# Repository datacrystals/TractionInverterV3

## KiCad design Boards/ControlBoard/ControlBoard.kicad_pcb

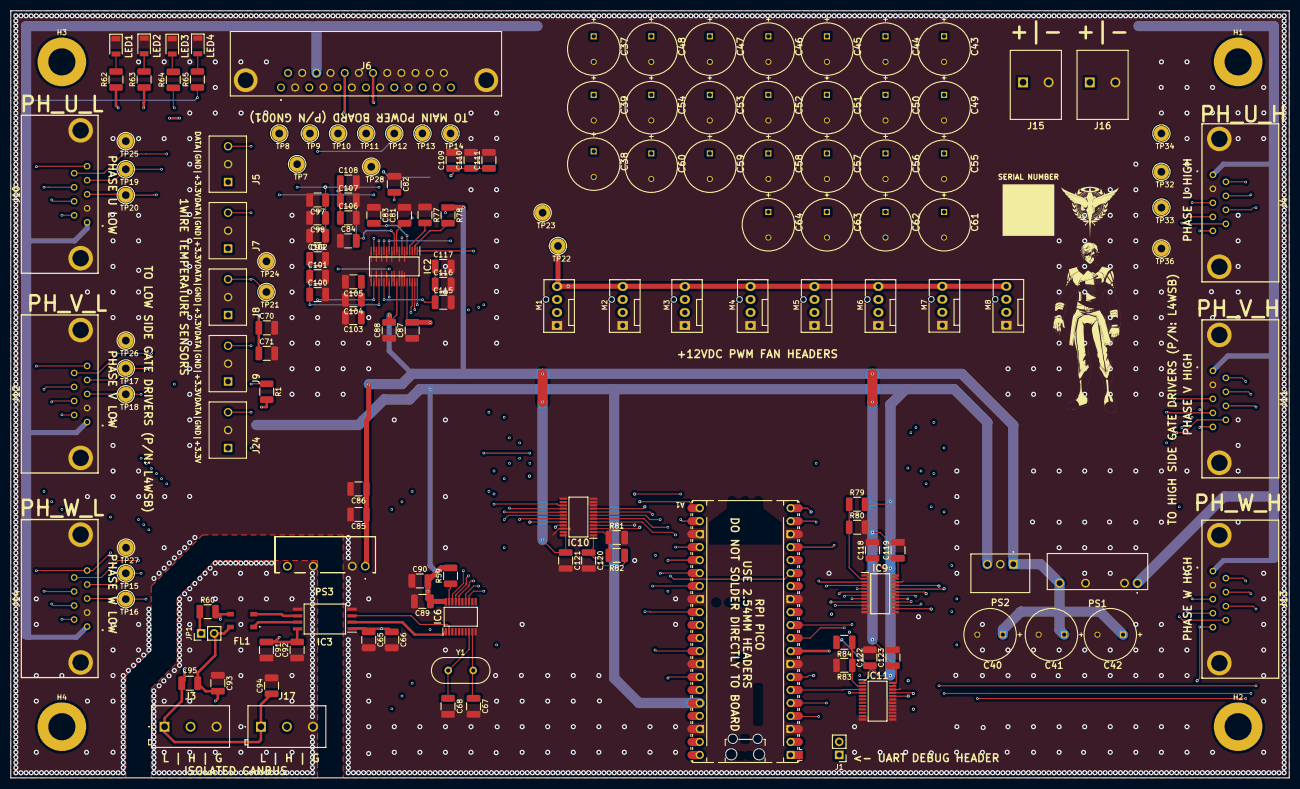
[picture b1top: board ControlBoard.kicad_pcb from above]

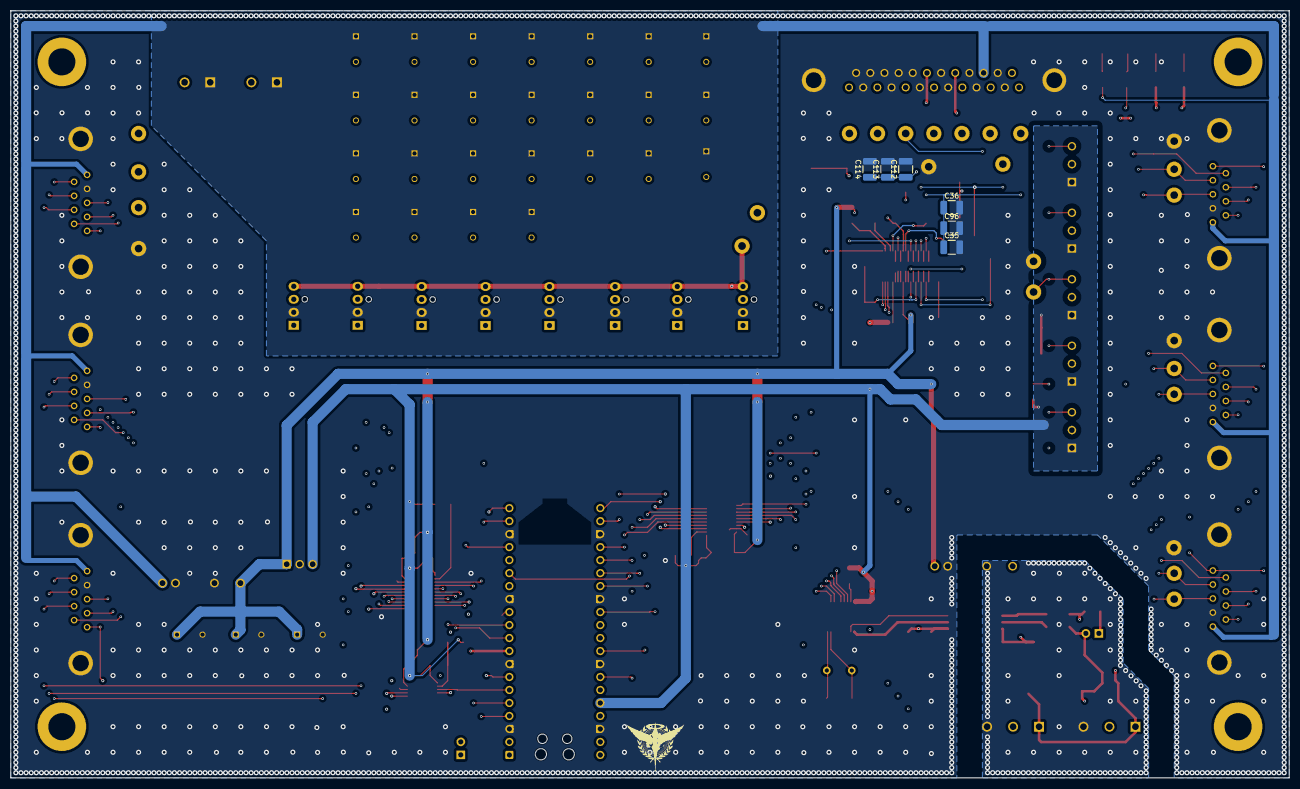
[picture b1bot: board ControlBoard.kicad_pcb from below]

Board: 4 copper layers, 250.0 x 150.0 mm, 166 parts (6 on the bottom side), 81 nets.

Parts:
A1: RaspberryPi_Pico; RaspberryPi_Pico_Common_Unspecified
C35, C97, C100, C103, C106, C109, C112, C115: 1nF; C_1210_3225Metric_Pad1.33x2.70mm_HandSolder
C36, C98, C101, C104, C107, C110, C113, C116: 10nF; C_1210_3225Metric_Pad1.33x2.70mm_HandSolder
C37, C38, C39, C40, C41, C42, C43, C44, C45, C46, C47, C48, C49, C50, C51, C52, C53, C54, C55, C56, C57, C58, C59, C60, C61, C62, C63, C64: UVY1E102MPD1TD; CAPPRD500W60D1025H1750
C65, C70, C81, C82, C83, C84, C85, C87, C88, C89, C92, C96, C99, C102, C105, C108, C111, C114, C117, C118, C119, C120, C121, C122, C123: 100nF; C_1210_3225Metric_Pad1.33x2.70mm_HandSolder
C66, C71, C86, C90, C91: 10uF; C_1210_3225Metric_Pad1.33x2.70mm_HandSolder
C67, C68, C93, C94, C95: 22pF; C_1210_3225Metric_Pad1.33x2.70mm_HandSolder
FL1: ACT45B-101-2P-TL003; ACT45B1012PTL003
H1, H2, H3, H4: MountingHole_Pad; MountingHole_5.3mm_M5_ISO7380_Pad
IC2: ADS8688AIDBT; SOP50P640X120-38M
IC3: ISO1042BDWVR; SOIC127P1150X280-8N
IC6: MCP2515-e_ST; SOP65P640X120-20N
IC9, IC10, IC11: SN74LXCH8T245PWR; SOP65P640X120-24N
J1: Conn_01x02_Pin; PinHeader_1x02_P2.54mm_Vertical
J3, J17: 1548129
J4, J10, J11, J12, J13, J14: 5-106505-2; 5-106505-2_3
J5, J7, J8, J9, J24: 5442251
J6: L717SDB25PA4CH3R
J15, J16: 1987724
JP1: Jumper_2_Open; PinHeader_1x02_P2.54mm_Vertical
LED1: LTST-C230CKT; LEDC3216X120N
LED2, LED3, LED4: LTST-C230GKT; LEDC3216X120N
M1, M2, M3, M4, M5, M6, M7, M8: Fan_4pin; FanPinHeader_1x04_P2.54mm_Vertical
PS1: RKE-1205S_H; RKE1205SH
PS2: R-78K3.3-1.0; R78K3310
PS3: RFMM-0505S; RFMM0505S
R1, R59, R77, R78, R79, R80, R81, R82, R83, R84: 4.7k; R_1210_3225Metric_Pad1.30x2.65mm_HandSolder
R60: 120; R_1210_3225Metric_Pad1.30x2.65mm_HandSolder
R62, R63, R64: 220; R_1210_3225Metric_Pad1.30x2.65mm_HandSolder
R65: 1k; R_1210_3225Metric_Pad1.30x2.65mm_HandSolder
TP7, TP8, TP9, TP10, TP11, TP12, TP13, TP14, TP15, TP16, TP17, TP18, TP19, TP20, TP21, TP22, TP23, TP24, TP25, TP26, TP27, TP28, TP32, TP33, TP34, TP36: TestPoint; TestPoint_Loop_D2.54mm_Drill1.5mm_Beaded
Y1: 8MHz; Crystal_HC49-4H_Vertical

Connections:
1WIRE_3v3_DATA: A1.20 (GPIO15), J5.3, J7.3, J8.3, J9.3, J24.3, R1.1, TP21.1
+3.3V: A1.36 (3V3), C65.1, C66.1, C70.1, C71.1, C87.2, C89.1, C90.2, C118.1, C120.1, C122.1, IC2.34 (DVDD), IC3.1 (VCC1), IC6.20 (VDD), IC9.1 (VCCA), IC10.1 (VCCA), IC11.1 (VCCA), J5.1, J7.1, J8.1, J9.1, J24.1, PS2.3 (+VOUT), R1.2, R59.2, R79.2, R82.2, R84.2
+5V: C40.1 (+), C41.1 (+), C42.1 (+), C81.1, C85.1, C86.1, C88.2, C119.1, C121.1, C123.1, IC2.9 (AVDD_1), IC2.30 (AVDD_2), IC9.23 (VCCB_1), IC9.24 (VCCB_2), IC10.23 (VCCB_1), IC10.24 (VCCB_2), IC11.23 (VCCB_1), IC11.24 (VCCB_2), PS1.7 (+VOUT), PS2.1 (+VIN), PS3.1 (+VIN), R64.1, R78.1
+12V: C37.1 (+), C38.1 (+), C39.1 (+), C43.1 (+), C44.1 (+), C45.1 (+), C46.1 (+), C47.1 (+), C48.1 (+), C49.1 (+), C50.1 (+), C51.1 (+), C52.1 (+), C53.1 (+), C54.1 (+), C55.1 (+), C56.1 (+), C57.1 (+), C58.1 (+), C59.1 (+), C60.1 (+), C61.1 (+), C62.1 (+), C63.1 (+), C64.1 (+), J4.1, J6.23, J10.1, J11.1, J12.1, J13.1, J14.1, J15.1, J16.1, M1.2 (+), M2.2 (+), M3.2 (+), M4.2 (+), M5.2 (+), M6.2 (+), M7.2 (+), M8.2 (+), PS1.1 (+VIN), R65.1
ADC_SPI_CS: A1.19 (GPIO14), IC2.38 (~CS)
CANBUS_ISO_5V: C91.1, C92.2, IC3.8 (VCC2), PS3.7 (+VOUT)
CANBUS_ISO_GND: C91.2, C92.1, C93.1, C94.2, IC3.5 (GND2), J3.3, J17.3, PS3.5 (-VOUT)
CAN_CS: A1.32 (GPIO27_ADC1), IC6.18 (~CS)
CAN_INT: A1.34 (GPIO28_ADC2), IC6.13 (~INT)
CanH_External: C93.2, C95.1, FL1.4, J3.2, J17.2, JP1.2 (B)
CanL_External: C94.1, C95.2, FL1.3, J3.1, J17.1, R60.2
DC_LINK_BUS_CURRENT_SENSE: C35.1, C36.1, C96.1, IC2.18 (AIN_1P), J6.1, TP8.1
DC_LINK_BUS_ISOLATED_VSENSE: C97.1, C98.1, C99.1, IC2.16 (AIN_0P), J6.25, TP7.1
FAN_3v3_PWM: A1.21 (GPIO16), IC10.3 (A1)
FAN_PWM: IC10.21 (B1), M1.4 (PWM), M2.4 (PWM), M3.4 (PWM), M4.4 (PWM), M5.4 (PWM), M6.4 (PWM), M7.4 (PWM), M8.4 (PWM), TP22.1
FAULT_3v3_INPUT: A1.31 (GPIO26_ADC0), IC11.4 (A2)
FAULT_INPUT: IC11.20 (B2), J4.5, J10.5, J11.5, J12.5, J13.5, J14.5
FAULT_LED: J6.21, R62.1
GATE_SPI_3v3_RX: A1.6 (GPIO4), IC11.3 (A1)
GATE_SPI_3v3_SCK: A1.4 (GPIO2), IC9.3 (A1)
GATE_SPI_3v3_TX: A1.5 (GPIO3), IC9.4 (A2)
GATE_SPI_RX: IC11.21 (B1), J4.6, J10.6, J11.6, J12.6, J13.6, J14.6, TP34.1
GATE_SPI_SCK: IC9.21 (B1), J4.8, J10.8, J11.8, J12.8, J13.8, J14.8, TP33.1
GATE_SPI_TX: IC9.20 (B2), J4.7, J10.7, J11.7, J12.7, J13.7, J14.7, TP32.1
GATE_U_3v3_H_CS: A1.9 (GPIO6), IC9.6 (A4)
GATE_U_3v3_L_CS: A1.7 (GPIO5), IC9.5 (A3)
GATE_U_H_CS: IC9.18 (B4), J4.9
GATE_U_L_CS: IC9.19 (B3), J10.9
GATE_V_3v3_H_CS: A1.11 (GPIO8), IC9.8 (A6)
GATE_V_3v3_L_CS: A1.10 (GPIO7), IC9.7 (A5)
GATE_V_H_CS: IC9.16 (B6), J11.9
GATE_V_L_CS: IC9.17 (B5), J12.9
GATE_W_3v3_H_CS: A1.17 (GPIO13), IC9.10 (A8)
GATE_W_3v3_L_CS: A1.12 (GPIO9), IC9.9 (A7)
GATE_W_H_CS: IC9.14 (B8), J13.9
GATE_W_L_CS: IC9.15 (B7), J14.9
GND: A1.3 (GND), A1.8 (GND), A1.13 (GND), A1.18 (GND), A1.23 (GND), A1.28 (GND), A1.33 (AGND), A1.38 (GND), C35.2, C36.2, C37.2 (-), C38.2 (-), C39.2 (-), C40.2 (-), C41.2 (-), C42.2 (-), C43.2 (-), C44.2 (-), C45.2 (-), C46.2 (-), C47.2 (-), C48.2 (-), C49.2 (-), C50.2 (-), C51.2 (-), C52.2 (-), C53.2 (-), C54.2 (-), C55.2 (-), C56.2 (-), C57.2 (-), C58.2 (-), C59.2 (-), C60.2 (-), C61.2 (-), C62.2 (-), C63.2 (-), C64.2 (-), C65.2, C66.2, C67.2, C68.2, C70.2, C71.2, C81.2, C82.1, C83.1, C84.1, C85.2, C86.2, C87.1, C88.1, C89.2, C90.1, C96.2, C97.2, C98.2, C99.2, C100.2, C101.2, C102.2, C103.2, C104.2, C105.2, C106.2, C107.2, C108.2, C109.2, C110.2, C111.2, C112.2, C113.2, C114.2, C115.2, C116.2, C117.2, C118.2, C119.2, C120.2, C121.2, C122.2, C123.2, IC2.6 (REFGND), IC2.8 (AGND_1), IC2.11 (AUX_GND), IC2.13 (AIN_6GND), IC2.15 (AIN_7GND), IC2.17 (AIN_0GND), IC2.19 (AIN_1GND), IC2.20 (AIN2_GND), IC2.22 (AIN_3GND), IC2.24 (AIN_4GND), IC2.26 (AIN_5GND), IC2.28 (AGND_2), IC2.29 (AGND_3), IC2.31 (AGND_4), IC2.32 (AGND_5), IC2.33 (DGND), IC3.4 (GND1), IC6.10 (VSS), IC9.11 (GND_1), IC9.12 (GND_2), IC9.13 (GND_3), IC9.22 (~OE), IC10.10 (A8), IC10.11 (GND_1), IC10.12 (GND_2), IC10.13 (GND_3), IC10.22 (~OE), IC11.11 (GND_1), IC11.12 (GND_2), IC11.13 (GND_3), IC11.14 (B8), IC11.15 (B7), IC11.16 (B6), IC11.17 (B5), IC11.18 (B4), IC11.19 (B3), IC11.22 (~OE), J4.2, J4.10, J4.11, J5.2, J6.2, J6.4, J6.6, J6.8, J6.10, J6.12, J6.14, J6.15, J6.16, J6.17, J6.18, J6.20, J6.22, J6.24, J6.MH1, J6.MH2, J7.2, J8.2, J9.2, J10.2, J10.10, J10.11, J11.2, J11.10, J11.11, J12.2, J12.10, J12.11, J13.2, J13.10, J13.11, J14.2, J14.10, J14.11, J15.2, J16.2, J24.2, LED1.1 (K), LED2.1 (K), LED3.1 (K), LED4.1 (K), M1.1 (-), M2.1 (-), M3.1 (-), M4.1 (-), M5.1 (-), M6.1 (-), M7.1 (-), M8.1 (-), PS1.2 (-VIN), PS1.5 (-VOUT), PS2.2 (GND), PS3.2 (-VIN), R77.1, R80.2, R81.2, R83.2, TP23.1, TP24.1, TP25.1, TP26.1, TP27.1, TP28.1, TP36.1
unnamed: A1.1 (GPIO0), J1.1
unnamed: A1.2 (GPIO1), J1.2
unnamed: C84.2, IC2.10 (AUX_IN)
unnamed: C82.2, IC2.7 (REFCAP)
unnamed: C83.2, IC2.5 (REFIO)
unnamed: IC2.4 (~REFSEL), R77.2
unnamed: IC2.2 (~RST/~PD), R78.2
unnamed: FL1.1, IC3.7 (CANH)
unnamed: FL1.2, IC3.6 (CANL)
unnamed: IC3.3 (RXD), IC6.2 (RXCAN)
unnamed: IC3.2 (TXD), IC6.1 (TXCAN)
unnamed: C67.1, IC6.9 (OSC1), Y1.2
unnamed: C68.1, IC6.8 (OSC2), Y1.1
unnamed: IC6.19 (~RESET), R59.1
unnamed: IC9.2 (DIR), R79.1, R80.1
unnamed: IC10.2 (DIR), R81.1, R82.1
unnamed: IC11.2 (DIR), R83.1, R84.1
unnamed: JP1.1 (A), R60.1
unnamed: LED1.2 (A), R62.2
unnamed: LED2.2 (A), R63.2
unnamed: LED3.2 (A), R64.2
unnamed: LED4.2 (A), R65.2
PHASE_U_ISENSE: C100.1, C101.1, C102.1, IC2.23 (AIN_3P), J6.3, TP9.1
PHASE_U_ISOLATED_VSENSE: C103.1, C104.1, C105.1, IC2.21 (AIN_2P), J6.9, TP12.1
PHASE_V_ISENSE: C106.1, C107.1, C108.1, IC2.27 (AIN_5P), J6.5, TP10.1
PHASE_V_ISOLATED_VSENSE: C115.1, C116.1, C117.1, IC2.25 (AIN_4P), J6.11, TP13.1
PHASE_W_ISENSE: C112.1, C113.1, C114.1, IC2.14 (AIN_7P), J6.7, TP11.1
PHASE_W_ISOLATED_VSENSE: C109.1, C110.1, C111.1, IC2.12 (AIN_6P), J6.13, TP14.1
PH_3v3_PWM_U_H: A1.26 (GPIO20), IC10.7 (A5)
PH_3v3_PWM_U_L: A1.22 (GPIO17), IC10.4 (A2)
PH_3v3_PWM_V_H: A1.27 (GPIO21), IC10.8 (A6)
PH_3v3_PWM_V_L: A1.24 (GPIO18), IC10.5 (A3)
PH_3v3_PWM_W_H: A1.29 (GPIO22), IC10.9 (A7)
PH_3v3_PWM_W_L: A1.25 (GPIO19), IC10.6 (A4)
PH_PWM_U_H: IC10.17 (B5), J4.3, J10.4, TP19.1
PH_PWM_U_L: IC10.20 (B2), J4.4, J10.3, TP20.1
PH_PWM_V_H: IC10.16 (B6), J11.3, J12.4, TP17.1
PH_PWM_V_L: IC10.19 (B3), J11.4, J12.3, TP18.1
PH_PWM_W_H: IC10.15 (B7), J13.3, J14.4, TP15.1
PH_PWM_W_L: IC10.18 (B4), J13.4, J14.3, TP16.1
SPI2_RX: A1.16 (GPIO12), IC2.36 (SDO), IC6.17 (SO)
SPI2_SCK: A1.14 (GPIO10), IC2.37 (SCLK), IC6.14 (SCK)
SPI2_TX: A1.15 (GPIO11), IC2.1 (SDI), IC6.16 (SI)
StatusLED: J6.19, R63.1

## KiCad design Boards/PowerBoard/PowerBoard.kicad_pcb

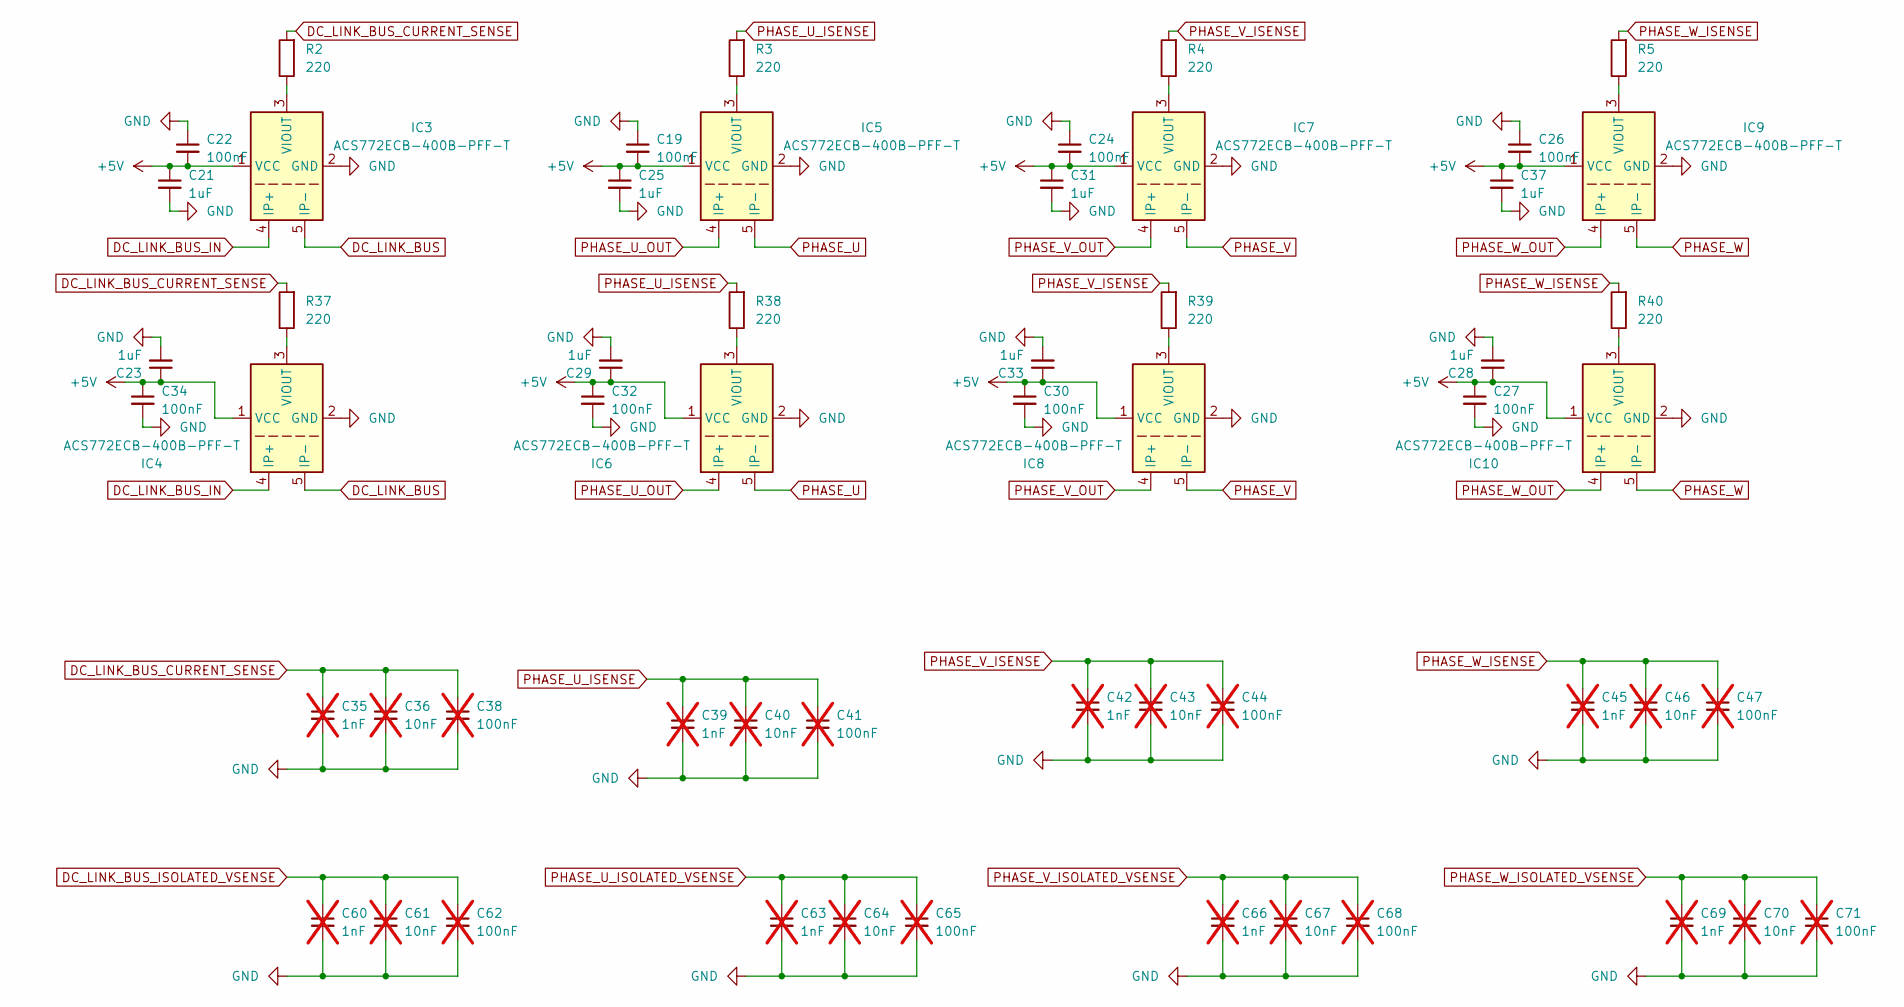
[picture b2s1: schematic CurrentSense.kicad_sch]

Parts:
C19, C22, C24, C26, C27, C30, C32, C34: 100nF; C_1210_3225Metric_Pad1.33x2.70mm_HandSolder
C21, C23, C25, C28, C29, C31, C33, C37: 1uF; C_1210_3225Metric_Pad1.33x2.70mm_HandSolder
C35, C39, C42, C45, C60, C63, C66, C69: 1nF; C_1210_3225Metric_Pad1.33x2.70mm_HandSolder; not fitted
C36, C40, C43, C46, C61, C64, C67, C70: 10nF; C_1210_3225Metric_Pad1.33x2.70mm_HandSolder; not fitted
C38, C41, C44, C47, C62, C65, C68, C71: 100nF; C_1210_3225Metric_Pad1.33x2.70mm_HandSolder; not fitted
IC3, IC4, IC5, IC6, IC7, IC8, IC9, IC10: ACS772ECB-400B-PFF-T; Allegro_CB_PFF; Mouser Part Number 250-772ECB400BPFFT
R2, R3, R4, R5, R37, R38, R39, R40: 220; R_1210_3225Metric_Pad1.30x2.65mm_HandSolder

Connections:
+5V: C19.2, C21.1, C22.2, C23.1, C24.2, C25.1, C26.2, C27.1, C28.1, C29.1, C30.1, C31.1, C32.1, C33.1, C34.1, C37.1, IC3.1 (VCC), IC4.1 (VCC), IC5.1 (VCC), IC6.1 (VCC), IC7.1 (VCC), IC8.1 (VCC), IC9.1 (VCC), IC10.1 (VCC); also elsewhere on the board
DC_LINK_BUS: IC3.5 (IP-), IC4.5 (IP-); also elsewhere on the board
DC_LINK_BUS_CURRENT_SENSE: C35.1, C36.1, C38.1, R2.2, R37.2; also elsewhere on the board
DC_LINK_BUS_IN: IC3.4 (IP+), IC4.4 (IP+); also elsewhere on the board
DC_LINK_BUS_ISOLATED_VSENSE: C60.1, C61.1, C62.1; also elsewhere on the board
GND: C19.1, C21.2, C22.1, C23.2, C24.1, C25.2, C26.1, C27.2, C28.2, C29.2, C30.2, C31.2, C32.2, C33.2, C34.2, C35.2, C36.2, C37.2, C38.2, C39.2, C40.2, C41.2, C42.2, C43.2, C44.2, C45.2, C46.2, C47.2, C60.2, C61.2, C62.2, C63.2, C64.2, C65.2, C66.2, C67.2, C68.2, C69.2, C70.2, C71.2, IC3.2 (GND), IC4.2 (GND), IC5.2 (GND), IC6.2 (GND), IC7.2 (GND), IC8.2 (GND), IC9.2 (GND), IC10.2 (GND); also elsewhere on the board
unnamed: IC3.3 (VIOUT), R2.1
unnamed: IC4.3 (VIOUT), R37.1
unnamed: IC5.3 (VIOUT), R3.1
unnamed: IC6.3 (VIOUT), R38.1
unnamed: IC7.3 (VIOUT), R4.1
unnamed: IC8.3 (VIOUT), R39.1
unnamed: IC9.3 (VIOUT), R5.1
unnamed: IC10.3 (VIOUT), R40.1
PHASE_U: IC5.5 (IP-), IC6.5 (IP-); also elsewhere on the board
PHASE_U_ISENSE: C39.1, C40.1, C41.1, R3.2, R38.2; also elsewhere on the board
PHASE_U_ISOLATED_VSENSE: C63.1, C64.1, C65.1; also elsewhere on the board
PHASE_U_OUT: IC5.4 (IP+), IC6.4 (IP+); also elsewhere on the board
PHASE_V: IC7.5 (IP-), IC8.5 (IP-); also elsewhere on the board
PHASE_V_ISENSE: C42.1, C43.1, C44.1, R4.2, R39.2; also elsewhere on the board
PHASE_V_ISOLATED_VSENSE: C66.1, C67.1, C68.1; also elsewhere on the board
PHASE_V_OUT: IC7.4 (IP+), IC8.4 (IP+); also elsewhere on the board
PHASE_W: IC9.5 (IP-), IC10.5 (IP-); also elsewhere on the board
PHASE_W_ISENSE: C45.1, C46.1, C47.1, R5.2, R40.2; also elsewhere on the board
PHASE_W_ISOLATED_VSENSE: C69.1, C70.1, C71.1; also elsewhere on the board
PHASE_W_OUT: IC9.4 (IP+), IC10.4 (IP+); also elsewhere on the board

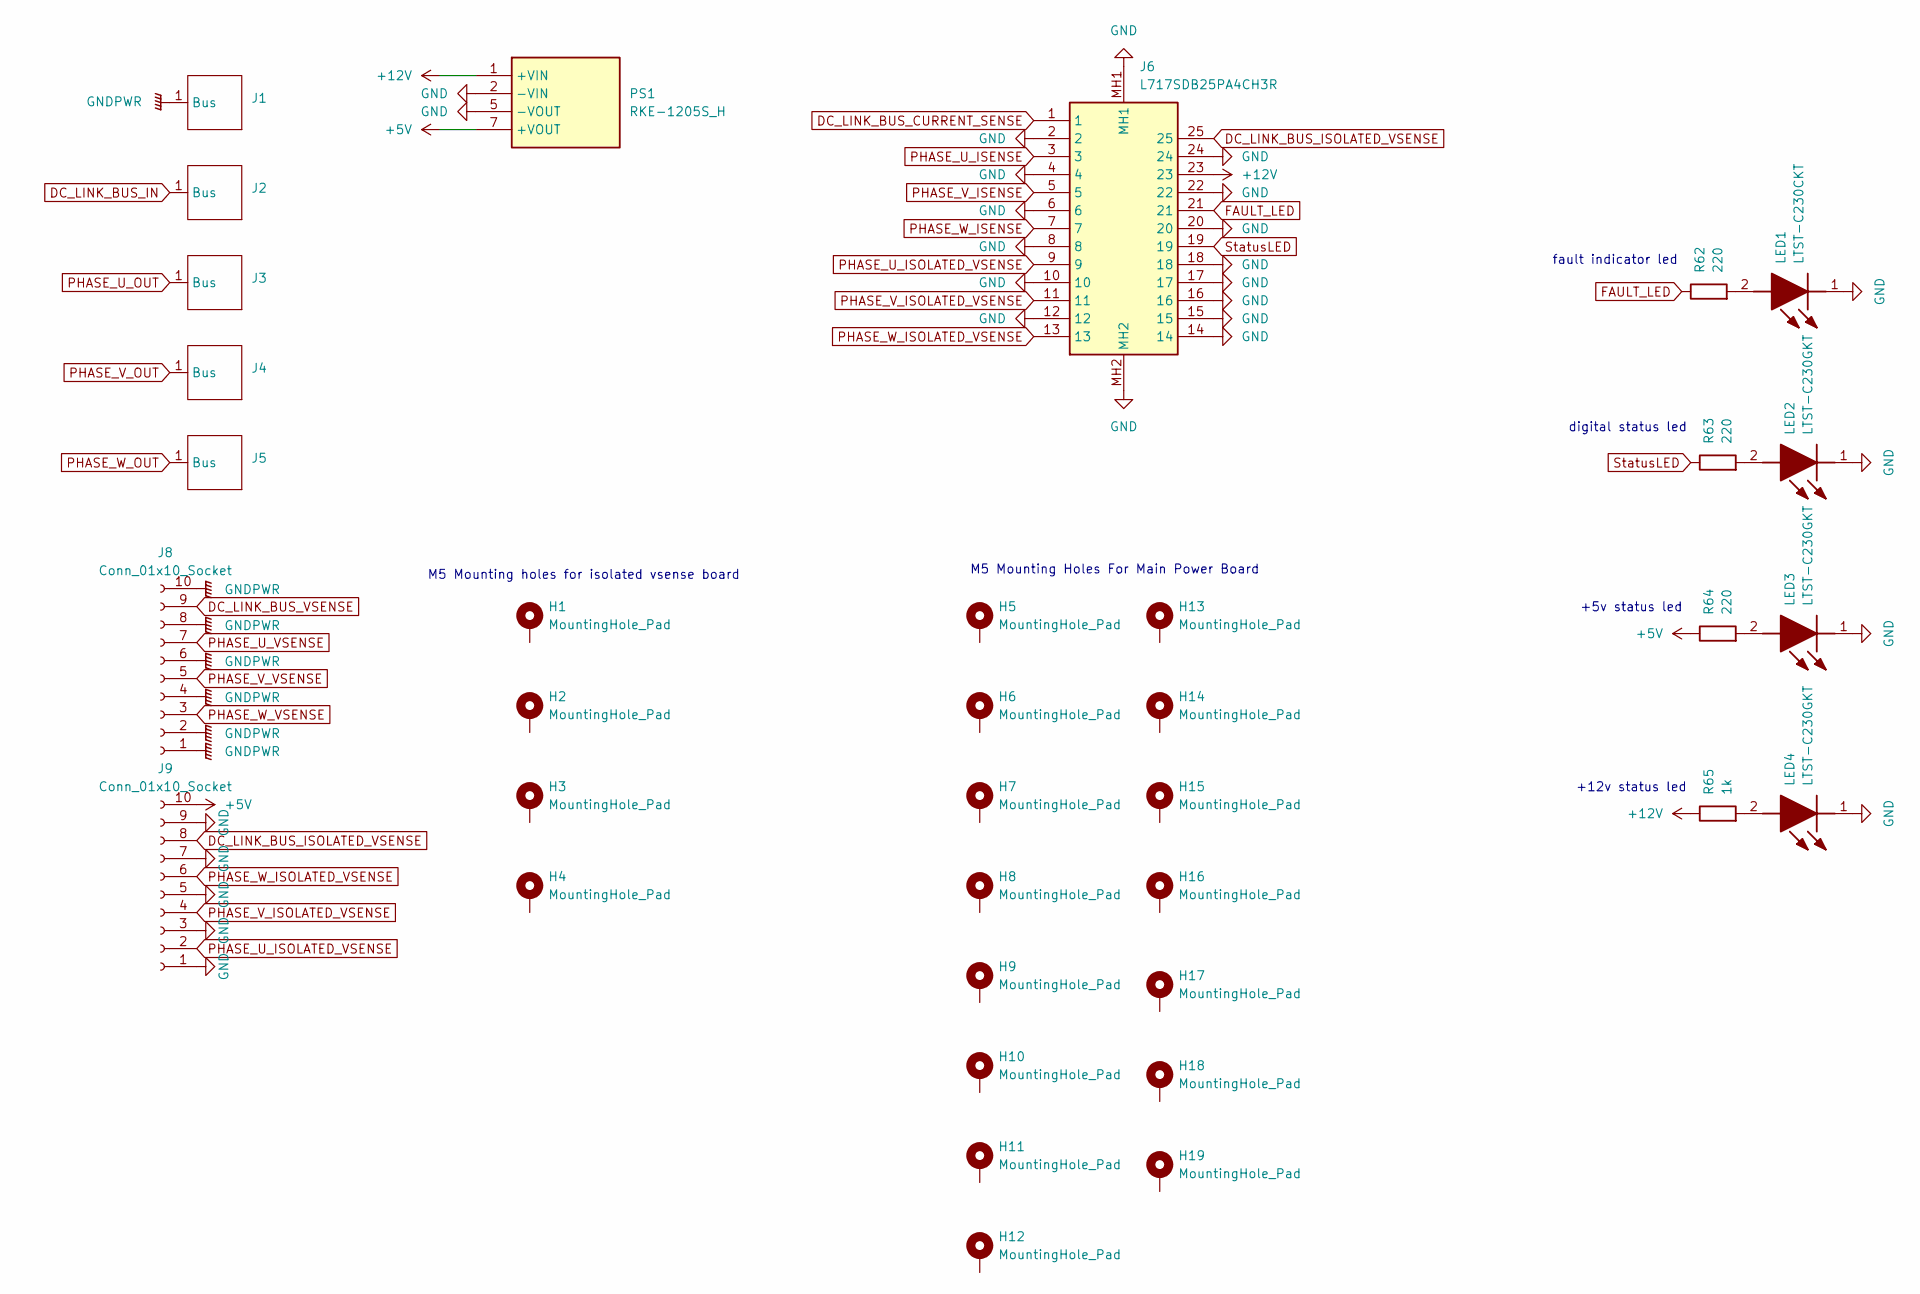
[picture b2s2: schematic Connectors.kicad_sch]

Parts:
H1, H2, H3, H4, H5, H6, H7, H8, H9, H10, H11, H12, H13, H14, H15, H16, H17, H18, H19: MountingHole_Pad; MountingHole_5.3mm_M5_ISO7380_Pad
J1, J2, J3, J4, J5: BusBarConnection
J6: L717SDB25PA4CH3R; Mouser Part Number 523-L717SDB25PA4CH3R
J8, J9: Conn_01x10_Socket; PinSocket_1x10_P2.54mm_Vertical
LED1: LTST-C230CKT; LEDC3216X120N; Mouser Part Number 859-LTST-C230CKT
LED2, LED3, LED4: LTST-C230GKT; LEDC3216X120N; Mouser Part Number 859-LTST-C230GKT
PS1: RKE-1205S_H; RKE1205SH; Mouser Part Number 919-RKE-1205S/H
R62, R63, R64: 220; R_1210_3225Metric_Pad1.30x2.65mm_HandSolder
R65: 1k; R_1210_3225Metric_Pad1.30x2.65mm_HandSolder

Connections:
+5V: J9.10, PS1.7 (+VOUT), R64.1; also elsewhere on the board
+12V: J6.23, PS1.1 (+VIN), R65.1
DC_LINK_BUS_CURRENT_SENSE: J6.1; also elsewhere on the board
DC_LINK_BUS_IN: J2.1 (Bus); also elsewhere on the board
DC_LINK_BUS_ISOLATED_VSENSE: J6.25, J9.8; also elsewhere on the board
DC_LINK_BUS_VSENSE: J8.9; also elsewhere on the board
FAULT_LED: J6.21, R62.1
GND: J6.2, J6.4, J6.6, J6.8, J6.10, J6.12, J6.14, J6.15, J6.16, J6.17, J6.18, J6.20, J6.22, J6.24, J6.MH1, J6.MH2, J9.1, J9.3, J9.5, J9.7, J9.9, LED1.1 (K), LED2.1 (K), LED3.1 (K), LED4.1 (K), PS1.2 (-VIN), PS1.5 (-VOUT); also elsewhere on the board
GNDPWR: J1.1 (Bus), J8.1, J8.2, J8.4, J8.6, J8.8, J8.10; also elsewhere on the board
unnamed: LED1.2 (A), R62.2
unnamed: LED2.2 (A), R63.2
unnamed: LED3.2 (A), R64.2
unnamed: LED4.2 (A), R65.2
PHASE_U_ISENSE: J6.3; also elsewhere on the board
PHASE_U_ISOLATED_VSENSE: J6.9, J9.2; also elsewhere on the board
PHASE_U_OUT: J3.1 (Bus); also elsewhere on the board
PHASE_U_VSENSE: J8.7; also elsewhere on the board
PHASE_V_ISENSE: J6.5; also elsewhere on the board
PHASE_V_ISOLATED_VSENSE: J6.11, J9.4; also elsewhere on the board
PHASE_V_OUT: J4.1 (Bus); also elsewhere on the board
PHASE_V_VSENSE: J8.5; also elsewhere on the board
PHASE_W_ISENSE: J6.7; also elsewhere on the board
PHASE_W_ISOLATED_VSENSE: J6.13, J9.6; also elsewhere on the board
PHASE_W_OUT: J5.1 (Bus); also elsewhere on the board
PHASE_W_VSENSE: J8.3; also elsewhere on the board
StatusLED: J6.19, R63.1

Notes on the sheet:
M5 Mounting Holes For Main Power Board
+12v status led
+5v status led
digital status led
M5 Mounting holes for isolated vsense board
fault indicator led

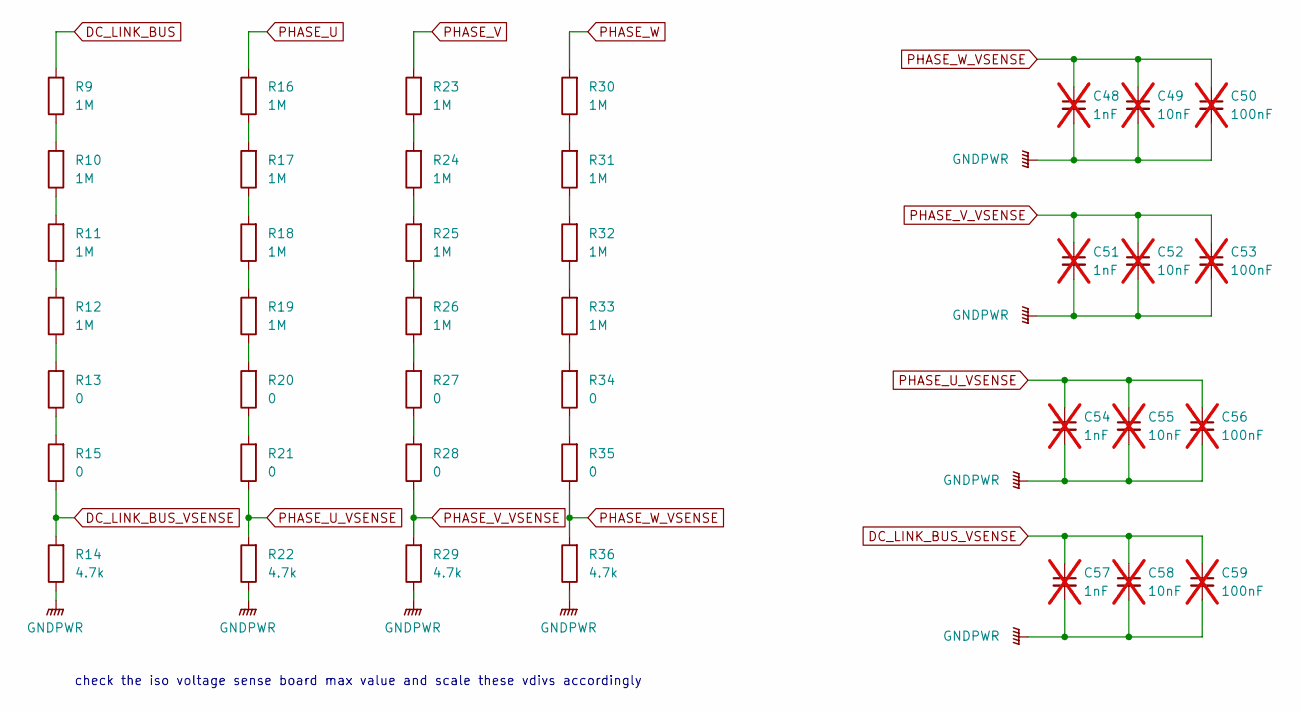
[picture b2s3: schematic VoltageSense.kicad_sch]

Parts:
C48, C51, C54, C57: 1nF; C_1210_3225Metric_Pad1.33x2.70mm_HandSolder; not fitted
C49, C52, C55, C58: 10nF; C_1210_3225Metric_Pad1.33x2.70mm_HandSolder; not fitted
C50, C53, C56, C59: 100nF; C_1210_3225Metric_Pad1.33x2.70mm_HandSolder; not fitted
R9, R10, R11, R12, R16, R17, R18, R19, R23, R24, R25, R26, R30, R31, R32, R33: 1M; R_1210_3225Metric_Pad1.30x2.65mm_HandSolder
R13, R15, R20, R21, R27, R28, R34, R35: 0; R_1210_3225Metric_Pad1.30x2.65mm_HandSolder
R14, R22, R29, R36: 4.7k; R_1210_3225Metric_Pad1.30x2.65mm_HandSolder

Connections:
DC_LINK_BUS: R9.2; also elsewhere on the board
DC_LINK_BUS_VSENSE: C57.1, C58.1, C59.1, R14.2, R15.1; also elsewhere on the board
GNDPWR: C48.2, C49.2, C50.2, C51.2, C52.2, C53.2, C54.2, C55.2, C56.2, C57.2, C58.2, C59.2, R14.1, R22.1, R29.1, R36.1; also elsewhere on the board
unnamed: R10.1, R11.2
unnamed: R9.1, R10.2
unnamed: R11.1, R12.2
unnamed: R12.1, R13.2
unnamed: R13.1, R15.2
unnamed: R16.1, R17.2
unnamed: R17.1, R18.2
unnamed: R18.1, R19.2
unnamed: R19.1, R20.2
unnamed: R20.1, R21.2
unnamed: R23.1, R24.2
unnamed: R24.1, R25.2
unnamed: R25.1, R26.2
unnamed: R26.1, R27.2
unnamed: R27.1, R28.2
unnamed: R30.1, R31.2
unnamed: R31.1, R32.2
unnamed: R32.1, R33.2
unnamed: R33.1, R34.2
unnamed: R34.1, R35.2
PHASE_U: R16.2; also elsewhere on the board
PHASE_U_VSENSE: C54.1, C55.1, C56.1, R21.1, R22.2; also elsewhere on the board
PHASE_V: R23.2; also elsewhere on the board
PHASE_V_VSENSE: C51.1, C52.1, C53.1, R28.1, R29.2; also elsewhere on the board
PHASE_W: R30.2; also elsewhere on the board
PHASE_W_VSENSE: C48.1, C49.1, C50.1, R35.1, R36.2; also elsewhere on the board

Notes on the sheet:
check the iso voltage sense board max value and scale these vdivs accordingly

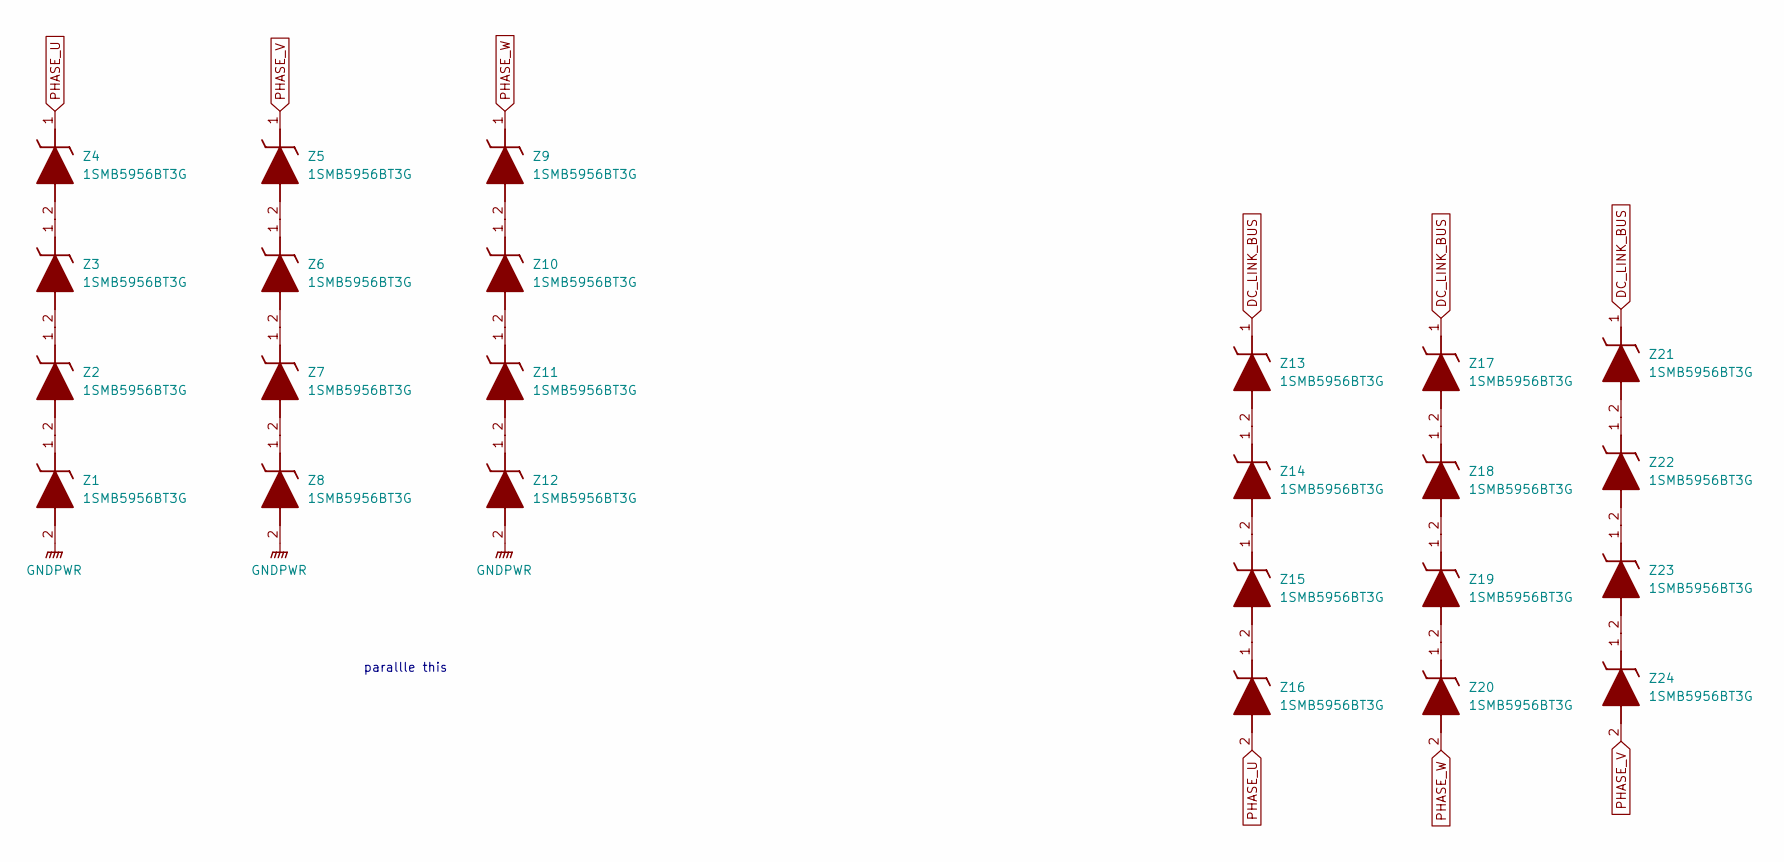
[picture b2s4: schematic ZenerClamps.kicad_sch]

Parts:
Z1, Z2, Z3, Z4, Z5, Z6, Z7, Z8, Z9, Z10, Z11, Z12, Z13, Z14, Z15, Z16, Z17, Z18, Z19, Z20, Z21, Z22, Z23, Z24: 1SMB5956BT3G; DIOM5436X247N; Mouser Part Number 863-1SMB5956BT3G

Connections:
DC_LINK_BUS: Z13.1 (K), Z17.1 (K), Z21.1 (K); also elsewhere on the board
GNDPWR: Z1.2 (A), Z8.2 (A), Z12.2 (A); also elsewhere on the board
unnamed: Z1.1 (K), Z2.2 (A)
unnamed: Z2.1 (K), Z3.2 (A)
unnamed: Z3.1 (K), Z4.2 (A)
unnamed: Z5.2 (A), Z6.1 (K)
unnamed: Z6.2 (A), Z7.1 (K)
unnamed: Z7.2 (A), Z8.1 (K)
unnamed: Z10.2 (A), Z11.1 (K)
unnamed: Z9.2 (A), Z10.1 (K)
unnamed: Z11.2 (A), Z12.1 (K)
unnamed: Z13.2 (A), Z14.1 (K)
unnamed: Z14.2 (A), Z15.1 (K)
unnamed: Z15.2 (A), Z16.1 (K)
unnamed: Z17.2 (A), Z18.1 (K)
unnamed: Z18.2 (A), Z19.1 (K)
unnamed: Z19.2 (A), Z20.1 (K)
unnamed: Z21.2 (A), Z22.1 (K)
unnamed: Z22.2 (A), Z23.1 (K)
unnamed: Z23.2 (A), Z24.1 (K)
PHASE_U: Z4.1 (K), Z16.2 (A); also elsewhere on the board
PHASE_V: Z5.1 (K), Z24.2 (A); also elsewhere on the board
PHASE_W: Z9.1 (K), Z20.2 (A); also elsewhere on the board

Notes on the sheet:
parallle this

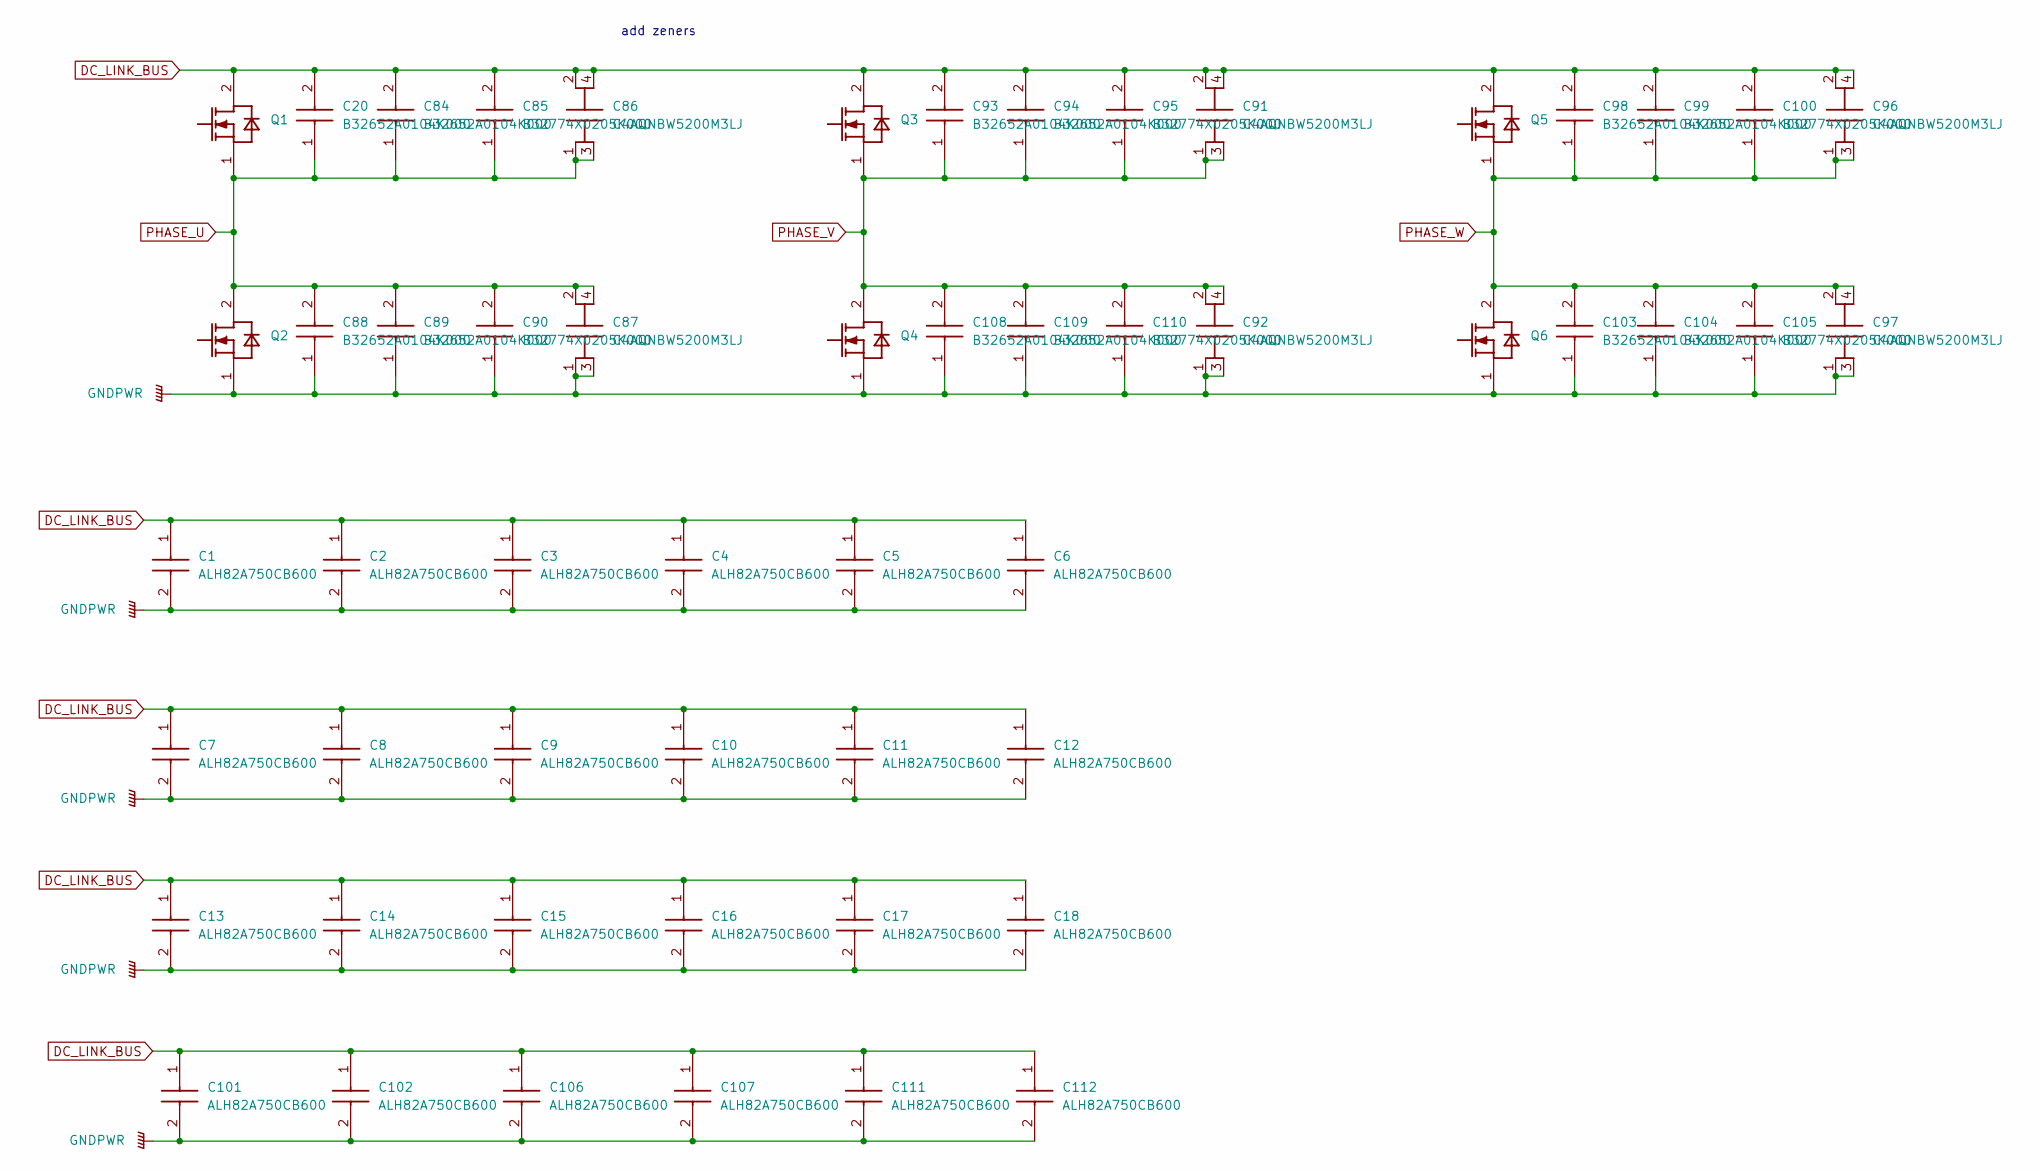
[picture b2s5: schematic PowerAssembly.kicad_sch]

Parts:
C1, C2, C3, C4, C5, C6, C7, C8, C9, C10, C11, C12, C13, C14, C15, C16, C17, C18, C101, C102, C106, C107, C111, C112: ALH82A750CB600; Mouser Part Number 80-ALH82A750CB600
C20, C84, C88, C89, C93, C94, C98, C99, C103, C104, C108, C109: B32652A0104K000; B32652__18_x_9_; Mouser Part Number 871-B32652A104K
C85, C90, C95, C100, C105, C110: B32774X0205K000; B32774X__31.5_x_12.5_; Mouser Part Number 871-B32774X0205K000
C86, C87, C91, C92, C96, C97: C4AQNBW5200M3LJ; Mouser Part Number 80-C4AQNBW5200M3LJ
Q1, Q2, Q3, Q4, Q5, Q6: CM600HA-24H-PWR

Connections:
DC_LINK_BUS: C1.1, C2.1, C3.1, C4.1, C5.1, C6.1, C7.1, C8.1, C9.1, C10.1, C11.1, C12.1, C13.1, C14.1, C15.1, C16.1, C17.1, C18.1, C20.2, C84.2, C85.2, C86.2, C86.4, C91.2, C91.4, C93.2, C94.2, C95.2, C96.2, C96.4, C98.2, C99.2, C100.2, C101.1, C102.1, C106.1, C107.1, C111.1, C112.1, Q1.2 (DRAIN), Q3.2 (DRAIN), Q5.2 (DRAIN); also elsewhere on the board
GNDPWR: C1.2, C2.2, C3.2, C4.2, C5.2, C6.2, C7.2, C8.2, C9.2, C10.2, C11.2, C12.2, C13.2, C14.2, C15.2, C16.2, C17.2, C18.2, C87.1, C87.3, C88.1, C89.1, C90.1, C92.1, C92.3, C97.1, C97.3, C101.2, C102.2, C103.1, C104.1, C105.1, C106.2, C107.2, C108.1, C109.1, C110.1, C111.2, C112.2, Q2.1 (POWER_SOURCE_5), Q4.1 (POWER_SOURCE_5), Q6.1 (POWER_SOURCE_5); also elsewhere on the board
PHASE_U: C20.1, C84.1, C85.1, C86.1, C86.3, C87.2, C87.4, C88.2, C89.2, C90.2, Q1.1 (POWER_SOURCE_5), Q2.2 (DRAIN); also elsewhere on the board
PHASE_V: C91.1, C91.3, C92.2, C92.4, C93.1, C94.1, C95.1, C108.2, C109.2, C110.2, Q3.1 (POWER_SOURCE_5), Q4.2 (DRAIN); also elsewhere on the board
PHASE_W: C96.1, C96.3, C97.2, C97.4, C98.1, C99.1, C100.1, C103.2, C104.2, C105.2, Q5.1 (POWER_SOURCE_5), Q6.2 (DRAIN); also elsewhere on the board

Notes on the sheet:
add zeners
